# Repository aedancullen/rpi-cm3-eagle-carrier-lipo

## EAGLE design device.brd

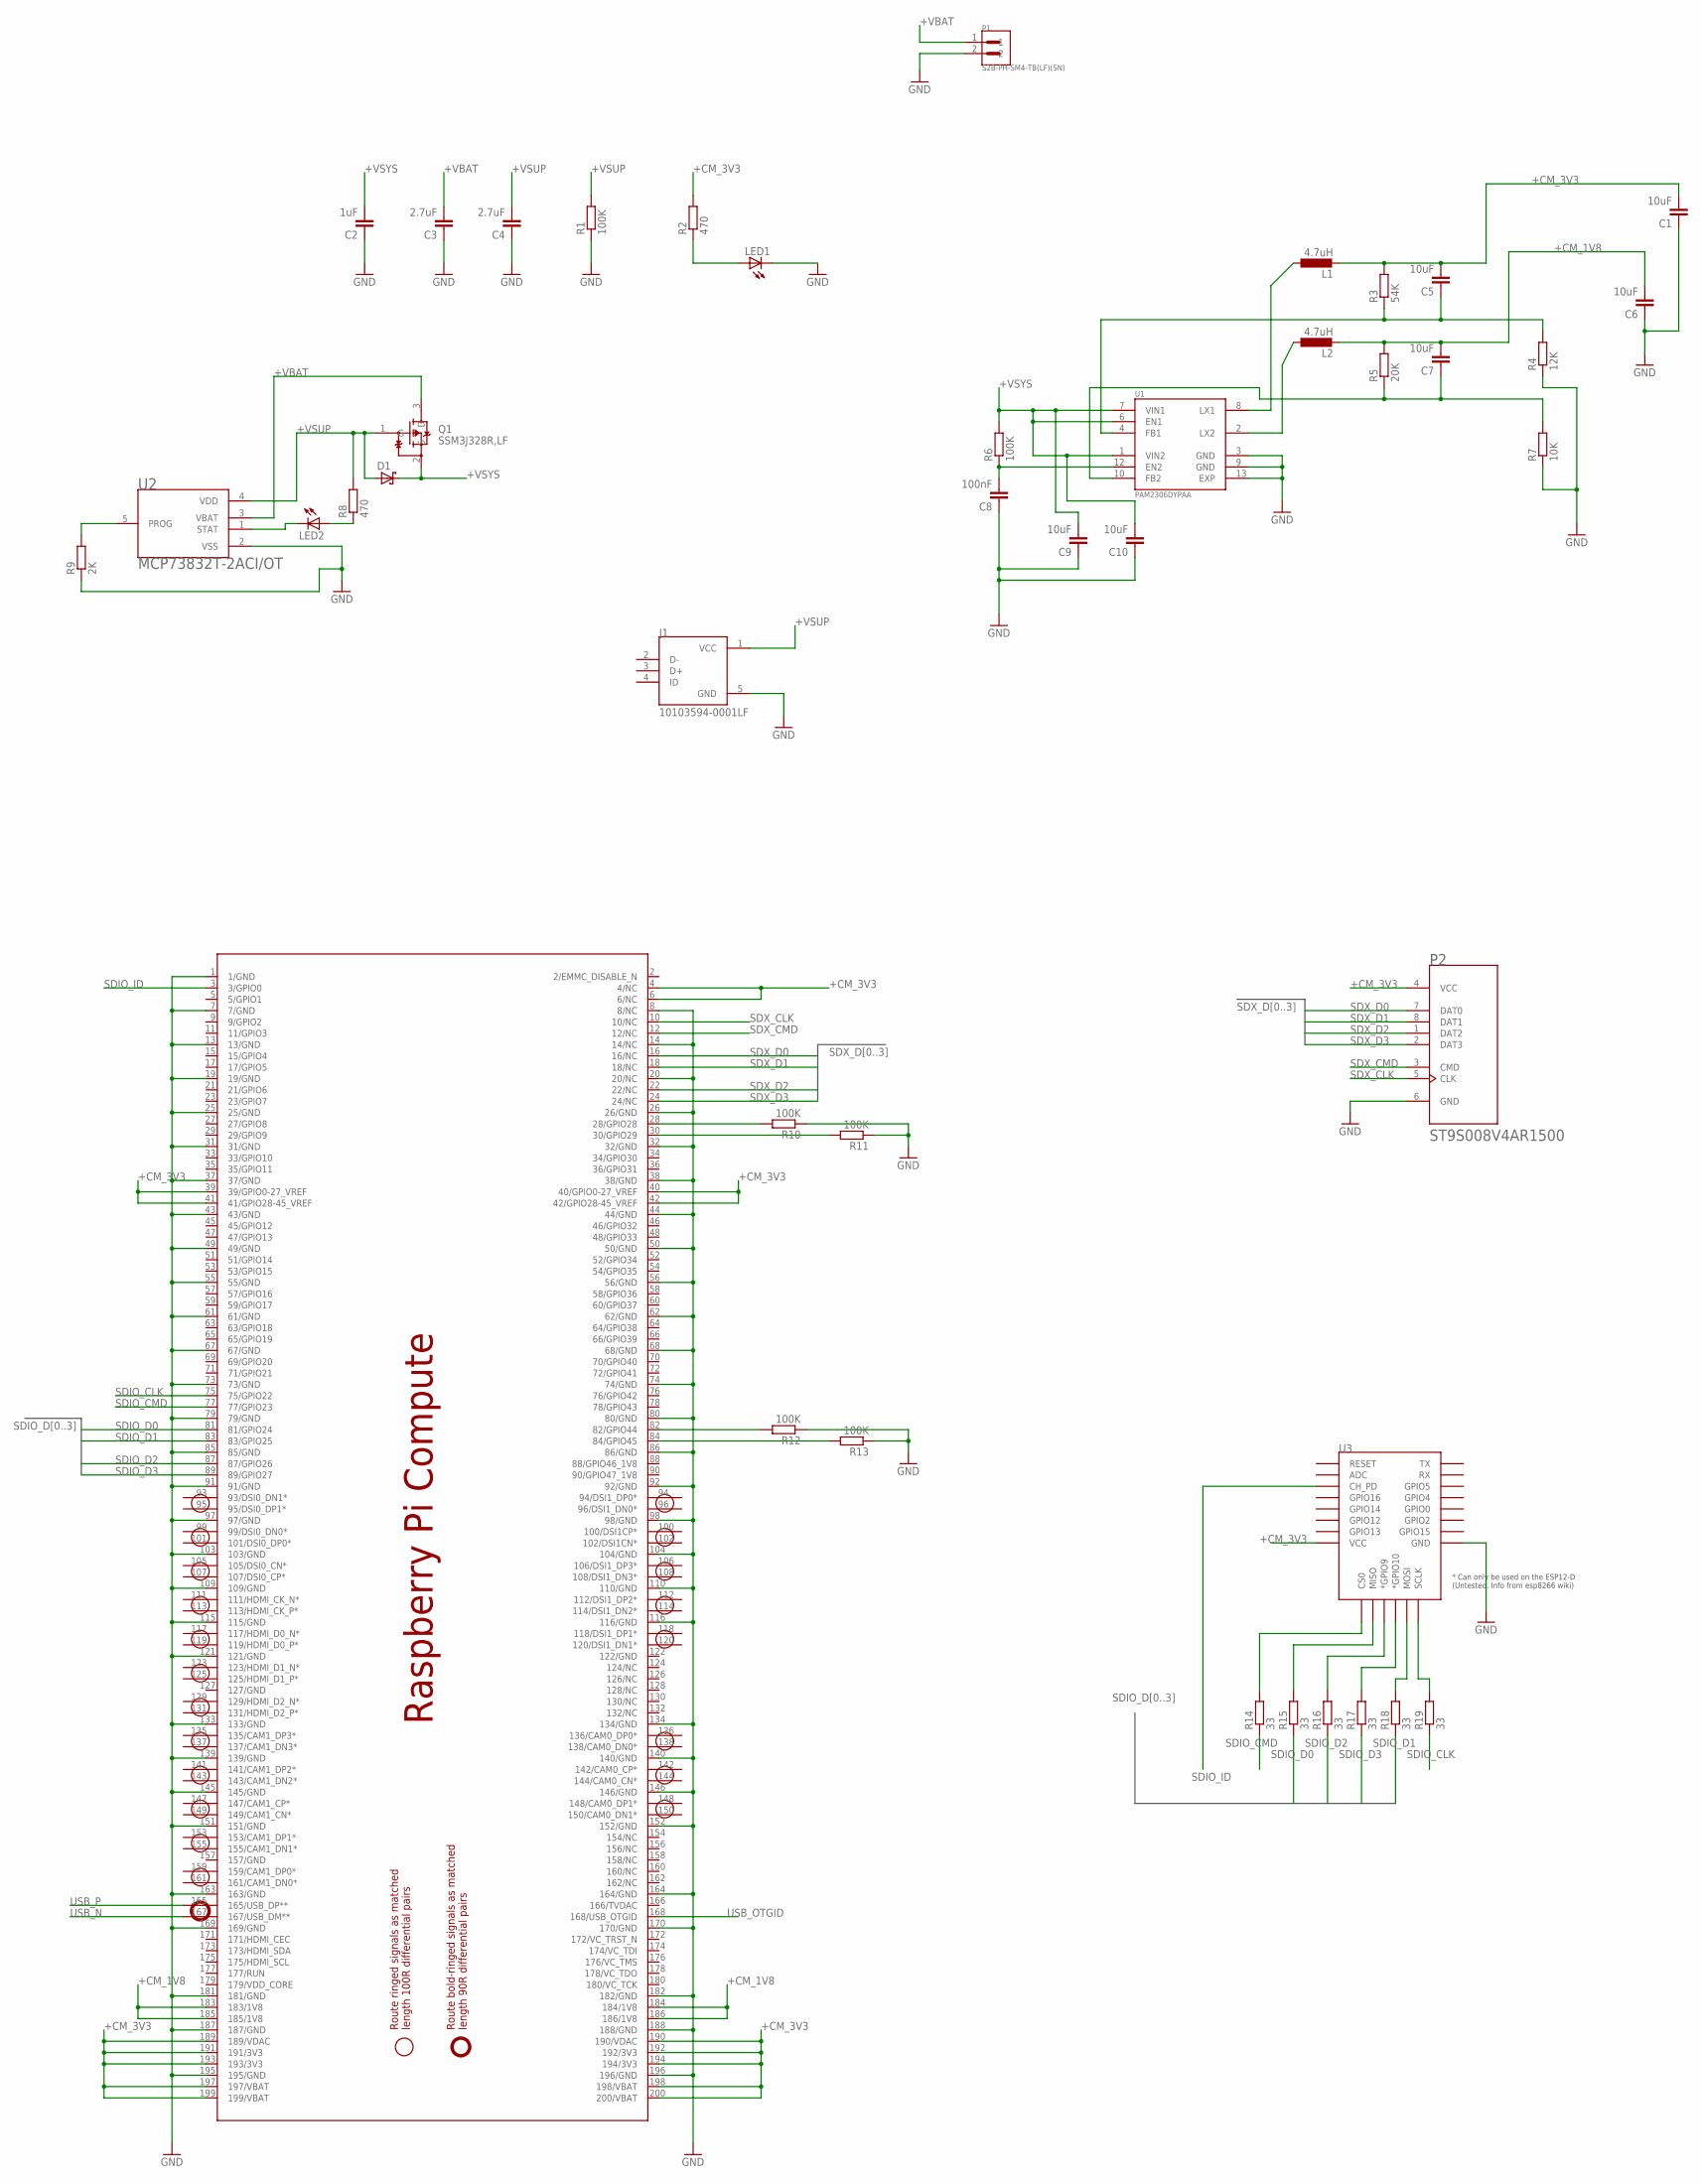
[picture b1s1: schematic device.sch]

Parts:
C1, C5, C6, C7, C9, C10: 10uF; C0603
C2: 1uF; C0603
C3, C4: 2.7uF; C0603
C8: 100nF; C0603
D1: SCHOTTKY-DIODESMD; SMB
J1: 10103594-0001LF; FCI_10103594-0001LF
L1, L2: 4.7uH; L1812
LED1, LED2: LEDCHIP-LED0603; CHIP-LED0603
P1: S2B-PH-SM4-TB(LF)(SN); JST_S2B-PH-SM4-TB(LF)(SN)
P2: ST9S008V4AR1500; JAE_ST9S008V4AR1500
PCB1: RPI_COMPUTE
Q1: SSM3J328R,LF; SOT95P240X88-3N
R1, R6, R10, R11, R12, R13: 100K; R0603
R2, R8: 470; R0603
R3: 54K; R0603
R4: 12K; R0603
R5: 20K; R0603
R7: 10K; R0603
R9: 2K; R0603
R14, R15, R16, R17, R18, R19: 33; R0603
U1: PAM2306DYPAA; SON45P300X300X80-13N
U2: MCP73832T-2ACI/OT; SOT95P270X145-5N
U3: ESP12ESMD; ESP12E-SMD

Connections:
+CM_1V8: C6.2, C7.2, L2.2, PCB1.183 (183/1V8), PCB1.184 (184/1V8), PCB1.185 (185/1V8), PCB1.186 (186/1V8), R5.2
+CM_3V3: C1.2, C5.2, L1.2, P2.4 (VCC), PCB1.4 (4/NC), PCB1.6 (6/NC), PCB1.39 (39/GPIO0-27_VREF), PCB1.40 (40/GPIO0-27_VREF), PCB1.41 (41/GPIO28-45_VREF), PCB1.42 (42/GPIO28-45_VREF), PCB1.189 (189/VDAC), PCB1.190 (190/VDAC), PCB1.191 (191/3V3), PCB1.192 (192/3V3), PCB1.193 (193/3V3), PCB1.194 (194/3V3), PCB1.197 (197/VBAT), PCB1.198 (198/VBAT), PCB1.199 (199/VBAT), PCB1.200 (200/VBAT), R2.2, R3.2, U3.VCC
+VBAT: C3.2, P1.1, Q1.3 (D), U2.3 (VBAT)
+VSUP: C4.2, D1.A, J1.1 (VCC), Q1.1 (G), R1.2, R8.2, U2.4 (VDD)
+VSYS: C2.2, C9.2, C10.2, D1.C, Q1.2 (S), R6.2, U1.1 (VIN2), U1.6 (EN1), U1.7 (VIN1)
GND: C1.1, C2.1, C3.1, C4.1, C6.1, C8.1, C9.1, C10.1, J1.5 (GND), LED1.C, P1.2, P2.6 (GND), PCB1.1 (1/GND), PCB1.7 (7/GND), PCB1.8 (8/NC), PCB1.13 (13/GND), PCB1.14 (14/NC), PCB1.19 (19/GND), PCB1.20 (20/NC), PCB1.25 (25/GND), PCB1.26 (26/GND), PCB1.31 (31/GND), PCB1.32 (32/GND), PCB1.37 (37/GND), PCB1.38 (38/GND), PCB1.43 (43/GND), PCB1.44 (44/GND), PCB1.49 (49/GND), PCB1.50 (50/GND), PCB1.55 (55/GND), PCB1.56 (56/GND), PCB1.61 (61/GND), PCB1.62 (62/GND), PCB1.67 (67/GND), PCB1.68 (68/GND), PCB1.73 (73/GND), PCB1.74 (74/GND), PCB1.79 (79/GND), PCB1.80 (80/GND), PCB1.85 (85/GND), PCB1.86 (86/GND), PCB1.91 (91/GND), PCB1.92 (92/GND), PCB1.97 (97/GND), PCB1.98 (98/GND), PCB1.103 (103/GND), PCB1.104 (104/GND), PCB1.109 (109/GND), PCB1.110 (110/GND), PCB1.115 (115/GND), PCB1.116 (116/GND), PCB1.121 (121/GND), PCB1.133 (133/GND), PCB1.134 (134/GND), PCB1.139 (139/GND), PCB1.140 (140/GND), PCB1.145 (145/GND), PCB1.146 (146/GND), PCB1.151 (151/GND), PCB1.152 (152/GND), PCB1.163 (163/GND), PCB1.164 (164/GND), PCB1.169 (169/GND), PCB1.170 (170/GND), PCB1.181 (181/GND), PCB1.182 (182/GND), PCB1.187 (187/GND), PCB1.188 (188/GND), PCB1.195 (195/GND), PCB1.196 (196/GND), R1.1, R4.1, R7.1, R9.1, R10.1, R11.1, R12.1, R13.1, U1.3 (GND), U1.9 (GND), U1.13 (EXP), U2.2 (VSS), U3.GND
unnamed: PCB1.84 (84/GPIO45), R13.2
unnamed: C8.2, R6.1, U1.12 (EN2)
unnamed: LED2.C, U2.1 (STAT)
unnamed: R9.2, U2.5 (PROG)
unnamed: LED2.A, R8.1
unnamed: PCB1.28 (28/GPIO28), R10.2
unnamed: PCB1.30 (30/GPIO29), R11.2
unnamed: C5.1, R3.1, R4.2, U1.4 (FB1)
unnamed: PCB1.82 (82/GPIO44), R12.2
unnamed: C7.1, R5.1, R7.2, U1.10 (FB2)
unnamed: L1.1, U1.8 (LX1)
unnamed: L2.1, U1.2 (LX2)
unnamed: LED1.A, R2.1
unnamed: R19.2, U3.SCLK
unnamed: R18.2, U3.MOSI
unnamed: R17.2, U3.GPIO10 (*GPIO10)
unnamed: R16.2, U3.GPIO9 (*GPIO9)
unnamed: R15.2, U3.MISO
unnamed: R14.2, U3.CS0
SDIO_CLK: PCB1.75 (75/GPIO22), R19.1
SDIO_CMD: PCB1.77 (77/GPIO23), R14.1
SDIO_D0: PCB1.81 (81/GPIO24), R15.1
SDIO_D1: PCB1.83 (83/GPIO25), R18.1
SDIO_D2: PCB1.87 (87/GPIO26), R16.1
SDIO_D3: PCB1.89 (89/GPIO27), R17.1
SDIO_ID: PCB1.3 (3/GPIO0), U3.CH_PD
SDX_CLK: P2.5 (CLK), PCB1.10 (10/NC)
SDX_CMD: P2.3 (CMD), PCB1.12 (12/NC)
SDX_D0: P2.7 (DAT0), PCB1.16 (16/NC)
SDX_D1: P2.8 (DAT1), PCB1.18 (18/NC)
SDX_D2: P2.1 (DAT2), PCB1.22 (22/NC)
SDX_D3: P2.2 (DAT3), PCB1.24 (24/NC)
USB_N: PCB1.167 (167/USB_DM**)
USB_OTGID: PCB1.168 (168/USB_OTGID)
USB_P: PCB1.165 (165/USB_DP**)

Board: 2 copper layers, 42 parts (29 on the bottom side), 38 nets, no tracks yet.

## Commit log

2017-07-16 Add schematic
2017-07-16 Add usb-c
2017-07-16 Rename to J1
2017-07-16 Add Wi-Fi
2017-07-16 Add board
2017-07-16 Modify board
2017-07-24 Modify layout and add PAM2306
